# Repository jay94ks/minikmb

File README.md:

# MiniKMB

[한국어](README.md) · [English](README.en.md)

두 대의 미니 PC를 하나의 관리 PC에서 다루기 위해 제작한 USB KVM 프로젝트입니다. HDMI 영상, 키보드·절대좌표 마우스, 시리얼, 가상 디스크와 네트워크 기능을 함께 제공합니다. RP2040 배선 프로토타입에서 시작해 STM32H7 기반 전용 PCB와 Rust 데스크톱 앱으로 발전했습니다.

[Windows 앱·펌웨어 다운로드](https://github.com/jay94ks/minikmb/releases) · [빌드 안내](docs/BUILDING.md) · [하드웨어와 주의사항](docs/HARDWARE.md) · [References](#references)

## 주요 기능

- 보드당 두 채널을 제공하며 여러 보드를 하나의 앱에서 관리합니다. USB 허브의 고정 포트 관계로 MCU와 MS2130을 자동으로 묶고, MCU와 통신해 읽은 UID를 채널 식별자로 사용합니다.
- 채널 이름 변경·저장, 카드 드래그 정렬, 영상 모드 선택과 한 채널의 영상 제어를 지원합니다.
- 실제 키보드, 가상 키보드, 특수 키, 절대좌표 마우스, 클릭·드래그·휠을 전달합니다.
- SD에 ISO/UDF 설치 이미지와 FAT32·exFAT·EXT4 디스크 이미지를 보관합니다. 광학 드라이브와 쓰기 가능한 가상 디스크, 폴더 전달, 이미지 업로드·생성·포맷을 관리합니다.
- CDC 시리얼, NCM 에뮬레이션·호스트 인터넷/LAN 공유, 포트 포워딩과 타깃 포트 스캐너를 제공합니다.
- ST-Link/SWD를 통한 STM32 플래싱과 RP2040 SPI Writer를 통한 MS2130 ROM 기록을 앱에서 실행합니다. 새 보드의 프로그래밍에 채널 선택이나 기존 MCU UID 등록은 필요하지 않습니다.
- 실행 중인 Rust 앱에 Windows Named Pipe로 연결하는 [로컬 CLI](kbm-rs/docs/CLI.md)를 제공합니다. 기본 입력·출력은 개별 옵션과 표·텍스트이며, `--json`으로 JSON을 선택합니다.
- 앱 내 REST 문서와 MCP 연동 안내를 제공합니다. 여러 API 키를 생성·개별 삭제할 수 있으며, 채널 정보·영상 캡처·키보드/마우스·TTY·MSC·NCM을 공통 명령 계층으로 제어합니다.

GUI·REST·MCP·CLI 전체에서 **활성 채널은 한 개**입니다. 채널 선택만 UID를 받고, 일반 제어는 현재 활성 채널에 적용합니다. 마우스 API 좌표는 캡처 영상의 픽셀이며 앱이 HID 절대좌표로 변환합니다. MCP를 켜면 REST도 함께 켜지고 REST 단독 실행도 가능합니다. 대용량 파일은 MCP가 알려주는 REST 업로드 끝점으로 전송합니다.

## 시작하기

1. [Releases](https://github.com/jay94ks/minikmb/releases)에서 Windows x64 ZIP을 받아 새 폴더에 풉니다. `tools/`, `firmware/`, 라이선스 파일을 함께 유지하고 `minikmb-native.exe`를 실행합니다.
2. 보드의 관리 USB **J9**를 관리 PC에 연결합니다. 타깃 0은 **J1 HDMI + J3 USB**, 타깃 1은 **J2 HDMI + J4 USB**를 연결합니다. J7/J8은 각 채널의 microSD입니다.
3. 채널 목록에서 **제어하기**를 누릅니다. 여러 보드를 연결해도 한 번에 한 채널의 영상을 엽니다.
4. 필요에 따라 디스크 공유·시리얼·네트워크 기능을 켭니다. REST/MCP와 네트워크 기능은 기본 OFF입니다.

Windows 10/11 x64, DirectX 12와 Media Foundation을 사용하는 미리보기 앱입니다. Visual C++ v14 x64 Runtime이 필요할 수 있습니다. 새 디스크 이미지의 파일시스템 생성은 WSL의 `mkfs`/`fsck` 도구를 사용합니다. 앱 자체 실행에는 Rust·Node.js·Python 설치가 필요하지 않습니다.

현재 배포 펌웨어는 **STM32 v1.0 / FS-HID r63**이며, Rust 앱 패키지 버전은 **0.1.0 preview**입니다. Electron v1.0 소스도 함께 보존합니다. 타깃 USB는 현재 Full Speed(FS)로 제공합니다. 설계자는 USB-C 삽입 방향 감지·신호 선택 회로의 부재와 그에 따른 HS 경로의 임피던스 불일치를, HS 연결이 안정적으로 수립되지 않거나 연결 후 오류율이 높았던 원인으로 판단하고 있습니다. 이 설계 회고와 검증 범위는 [HS 제한 및 설계 회고](docs/KNOWN-ISSUES.md#타깃-usb-hs와-설계-회고)에 정리했습니다. MS2130의 USB 3.x 영상 경로와 MCU의 USB3300/ULPI 경로는 서로 별개입니다. 자세한 범위는 [알려진 제한](docs/KNOWN-ISSUES.md)을 확인해 주세요.

## 로컬 CLI (최신 소스)

업데이트된 GUI와 `minikmb-cli.exe`를 함께 빌드하면 TCP REST/MCP를 켜거나 API 키를 만들지 않고도 같은 기능을 사용할 수 있습니다. `channels`, `activate UID`, `capture`, 파일 업로드와 이벤트 구독을 제공하며, 61개 공통 API 명령을 `COMMAND --field value` 또는 `call COMMAND`로 호출합니다.

```powershell
.\minikmb-cli.exe channels
.\minikmb-cli.exe schema hid_key_sequence
.\minikmb-cli.exe hid_key_sequence --keys a --keys b --keys c
.\minikmb-cli.exe channels --json
```

키 입력 명령은 활성 타깃을 실제로 제어합니다. [한글 사용법](kbm-rs/docs/CLI.md) · [English](kbm-rs/docs/CLI.en.md). AI 에이전트용 [SKILL.md](kbm-rs/packaging/SKILL.md)도 배포 폴더에 함께 포함합니다. CLI와 에이전트 스킬·REST 문서·독립 HTML 콘솔은 [v1.0.1 릴리스](https://github.com/jay94ks/minikmb/releases/tag/v1.0.1)부터 포함됩니다. [빌드 안내](docs/BUILDING.md)를 참고하세요.

REST 전체 요청의 인자와 예시는 [REST API 문서](kbm-rs/packaging/REST-API.md), 정확한 스키마는 [OpenAPI](kbm-rs/packaging/openapi.json)에 있습니다. [HTML 요청 콘솔](kbm-rs/packaging/REST-API.html)도 함께 배포합니다. HTML 파일을 직접 열고 앱의 REST 주소와 API 키를 입력하면 실제 요청을 실행할 수 있습니다. 별도 웹서버는 필요 없습니다.

## 문서 언어

공개 안내문서는 [한글 문서](docs/README.md)와 [영문 문서](docs/README.en.md)에서 각각 찾을 수 있습니다. 각 안내문서 상단에서 언어를 전환할 수 있습니다. 프로토콜 상세 명세·소스 주석은 개발 참고자료로 연결하고, 제조사 데이터시트와 외부 라이선스 원문은 원래 언어로 보존합니다.

## 개발 과정과 사진

### RP2040 프로토타입

초기 구성은 관리용 RP2040 한 대와 타깃용 RP2040 두 대를 UART로 연결했습니다. HDMI 영상은 별도의 상용 캡처 케이블 두 개를 사용했습니다. 아래 사진은 수작업 배선 프로토타입과 미니 PC 두 대에 설치해 시험했던 구성입니다.

| RP2040 배선 프로토타입 | 상용 캡처 케이블을 사용한 두 대의 미니 PC 시험 |
|---|---|
|  |  |

### STM32H7 기반 전용 보드

새 버전에서는 STM32H743 두 개, USB3300 PHY 두 개, MS2130 캡처 IC 두 개, USB 허브와 microSD 슬롯을 한 PCB에 통합했습니다. MCU 펌웨어는 TinyUSB·FreeRTOS·FatFs를 이용합니다.

| 디버깅·펌웨어 개발 단계 | 미니 PC 두 대에 연결한 전용 보드 |
|---|---|
|  |  |

### H7 보드를 위한 MS2130 ROM 플래싱 도구와 SMT 검사

왼쪽 도구는 **STM32H7 보드에 탑재한 MS2130을 실제로 동작시키기 위해 제작한 RP2040 기반 SPI ROM Writer**입니다. 초기 KVM 프로토타입과는 역할이 다릅니다. 외부 SPI 플래시에 MS2130 펌웨어를 기록한 뒤 영상 입력이 동작했습니다. 오른쪽은 SMT 조립 공정 이후 촬영한 X-ray입니다. 사진 자체를 보드 전체의 전기적·신호 무결성 검증 결과로 해석하지는 않습니다.

| MS2130용 SPI ROM Writer | SMT 조립 후 X-ray |
|---|---|
|  |  |

### PC 앱

Electron 앱을 바탕으로 Rust·egui 앱을 구현했습니다. 채널을 묶어 관리하고, 선택한 타깃의 영상과 입력·저장소·네트워크를 제어합니다. 아래는 채널 목록과 MCP 연동 안내 화면입니다. 스크린샷은 개발 당시의 장치 상태를 보여 줍니다.

## 저장소 구성

| 위치 | 내용 |
|---|---|
| [`hardware/stm32h7/`](hardware/stm32h7/) | 실제 제작한 6층 PCB·회로도·프로젝트 로컬 라이브러리·Gerber·조립 BOM/CPL |
| [`hardware/case/`](hardware/case/) | 나사 없는 투명 케이스 시안, FreeCAD 원본과 JLC3DP용 STL·STEP |
| [`hardware/rp2040/`](hardware/rp2040/) | 수작업 RP2040 프로토타입 배선 안내 |
| [`hardware/prototypes/`](hardware/prototypes/) | 초기 부품 라이브러리와 미완성 MS2130 단독 시험 보드. 제조용 아님 |
| [`firmware/stm32h7/`](firmware/stm32h7/) | 현재 STM32H743 펌웨어, STM32CubeIDE 프로젝트, 프로토콜·메모리맵·테스트 |
| [`master/`](master/), [`slave/kbm-slave/`](slave/kbm-slave/), [`common/`](common/) | RP2040 관리 브리지·타깃 펌웨어와 공통 프로토콜/호스트 테스트 |
| [`firmware/flash-writer/`](firmware/flash-writer/) | RP2040 SPI Writer 펌웨어와 호스트 도구 소스 |
| [`kbm/`](kbm/) | Electron·Quasar·Vue·TypeScript 앱 |
| [`kbm-rs/`](kbm-rs/) | 현재 Rust·egui·wgpu 앱, 로컬 CLI와 REST/MCP 서버 |
| [`work/`](work/) | 하드웨어 입력을 발생시키지 않는 회귀 테스트와 앱 빌드 보조 도구 |
| [`vendor/`](vendor/) | 고정 라이브러리 원본 아카이브, SDK, GPL 대응 소스와 체크섬 |
| [`references/`](references/) | 사용 칩셋 목록·데이터시트·출처·자료별 권리 고지 |
| [`docs/`](docs/) | 빌드·사용 범위·하드웨어 설명과 개발 사진 |

원래 RP2040 소스의 상대 경로를 유지하기 위해 `master`/`slave`/`common`과 두 앱의 디렉터리 이름을 유지했습니다. 빌드 캐시, 개인 설정·API 키, 장치 캡처 로그, 프롬프트·대화 기록은 공개 소스에 포함하지 않습니다.

## 개발 및 검증

[빌드 안내](docs/BUILDING.md)에 Windows 앱, WSL RP2040, STM32CubeIDE와 포터블 ARM 빌드 절차를 정리했습니다. 하드웨어와 독립적인 테스트는 [테스트 안내](docs/TESTING.md)를 참조해 주세요. 단위 테스트 통과, 펌웨어 빌드, 실제 타깃 동작 확인은 구분합니다.

**회로도는 제작자 jay94ks가 직접 작성했습니다.** 타깃 USB-C의 방향 감지·신호 선택 구성과 HS 경로의 임피던스 조건을 충분히 검토하지 않은 채 PCB 아트웍으로 진행한 것이 이번 설계의 검토 누락이었습니다. 이 문제를 GPT가 회로도를 잘못 작성한 결과로 기록하지 않습니다.

이 프로젝트는 **OpenAI Codex의 GPT 6 Astra와 Sol을 활용하여 개발**했습니다. 제작자가 회로도 작성·하드웨어 제작·연결·납땜·실사용 확인을 수행했으며, 두 모델은 PCB 배치·배선 작업, 펌웨어·앱 구현과 문서화에 활용했습니다.

## 라이선스

직접 작성한 코드와 설계·문서는 [MIT License](LICENSE)로 공개합니다. **아래 외부 구성 요소까지 MIT로 재허가하는 것은 아닙니다.** 원래 저작권·라이선스·예외 조항이 우선하며, 자료별 적용 범위는 [라이선스 고지](NOTICE.ko.md)와 [References](references/README.md)에 정리했습니다.

| 구성 요소 | 적용 조건과 고지 |
|---|---|
| MiniKMB 직접 작성 코드·설계·문서 | MIT. 기존 외부 코드/데이터와 개별 SPDX 고지는 제외 |
| TinyUSB, FreeRTOS | MIT. 원본 LICENSE 보존 |
| Pico SDK, STM32 HAL, CMSIS | SDK/파일별 BSD-3-Clause·Apache-2.0 등 원문 조건 보존 |
| FatFs | ChaN의 원래 저작권 및 허용 고지 보존 |
| Rust·Electron 의존성 | lock 파일로 고정. [원본 아카이브](vendor/README.md)와 각 패키지의 LICENSE/NOTICE, [Windows 앱 의존성 고지](kbm-rs/licenses/THIRD-PARTY.md) 참조 |
| probe-rs | MIT OR Apache-2.0. 앱에서 별도 실행 파일로 호출 |
| flashrom·MS2130 SPI helper | GPL-2.0 계열/파일별 고지. [대응 소스](vendor/flashrom/)와 원래 COPYING 포함. 별도 프로세스로 실행 |
| Noto Sans KR / Lucide | SIL OFL-1.1 / ISC 및 MIT(Feather 유래 부분). [글꼴·아이콘 고지](kbm-rs/assets/fonts/) 참조 |
| KiCad 표준 라이브러리·공급사 유래 형상 | 원래 라이선스와 KiCad 예외/공급사 출처 고지 보존. [CAD 출처](hardware/stm32h7/libraries/README.md) 참조 |
| 데이터시트·칩셋 문서·MS2130 ROM | 제조사/원 저작권자의 권리 유지. MIT 대상 아님. MS2130 ROM의 별도 공개 라이선스는 확인되지 않음 |

프로젝트 사진은 제작자가 공개용으로 제공한 개발 기록입니다. 제품명·상표·화면에 보이는 외부 소프트웨어의 권리는 해당 권리자에게 있습니다.

## References

칩셋 목록과 회로도 참조번호는 [chipsets.csv](references/chipsets.csv), 수집한 원문과 SHA-256은 [데이터시트 목록](references/README.md), 라이브러리 버전·원본은 [vendor/README.md](vendor/README.md)에 있습니다. 다운로드할 수 없었던 자료도 원본 링크와 상태를 남겼습니다.

- **STM32H743** — [ST 데이터시트](https://www.st.com/resource/en/datasheet/stm32h743vi.pdf), [RM0433](https://www.st.com/resource/en/reference_manual/rm0433-stm32h742-stm32h743753-and-stm32h750-value-line-advanced-armbased-32bit-mcus-stmicroelectronics.pdf)
- **USB3300** — [Microchip DS00001783](https://ww1.microchip.com/downloads/aemDocuments/documents/UNG/ProductDocuments/DataSheets/USB3300-Data-Sheet-DS00001783.pdf)
- **MS2130 / GL3510-OSY52 / CH482X** — [수집한 데이터시트와 공급처 출처](references/README.md). 초기 검토용 GL3523 자료는 실제 GL3510 부품과 구분합니다.
- **LM26480 / TUSB321 / XC6220 / USBLC6-2 / W25Q16JV** — [칩셋·전원·보호·SPI 메모리 자료](references/README.md)
- **RP2040 / Pico SDK** — [RP2040 데이터시트](https://datasheets.raspberrypi.com/rp2040/rp2040-datasheet.pdf), [Pico SDK](https://github.com/raspberrypi/pico-sdk)
- **TinyUSB / FreeRTOS / FatFs / CMSIS / STM32 HAL** — [hathach/tinyusb](https://github.com/hathach/tinyusb), [FreeRTOS-Kernel](https://github.com/FreeRTOS/FreeRTOS-Kernel), [FatFs](https://elm-chan.org/fsw/ff/), [CMSIS](https://github.com/ARM-software/CMSIS_5), [STM32H7 HAL](https://github.com/STMicroelectronics/stm32h7xx-hal-driver)
- **PC 앱** — [egui/eframe](https://github.com/emilk/egui), [wgpu](https://github.com/gfx-rs/wgpu), [Tokio](https://tokio.rs/), [Axum](https://github.com/tokio-rs/axum), [Rust MCP SDK](https://github.com/modelcontextprotocol/rust-sdk), [smoltcp](https://github.com/smoltcp-rs/smoltcp), [Electron](https://www.electronjs.org/), [Quasar](https://quasar.dev/), [Vue](https://vuejs.org/)
- **플래싱 도구** — [probe-rs](https://github.com/probe-rs/probe-rs), [flashrom](https://github.com/flashrom/flashrom)
- **PCB 제작 검토** — [JLCPCB capabilities](https://jlcpcb.com/capabilities/pcb-capabilities), [임피던스 계산기](https://jlcpcb.com/pcb-impedance-calculator). 저장된 스택업·제조 조건은 [하드웨어 안내](docs/HARDWARE.md) 참조

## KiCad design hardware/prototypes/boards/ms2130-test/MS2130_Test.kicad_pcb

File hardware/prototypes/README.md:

# Early hardware studies

This directory preserves early candidate symbols, footprints, pin maps and the incomplete MS2130 test board. These are historical studies, not the fabricated STM32H7 board. The MS2130 test PCB is not fully routed and must not be submitted for fabrication as a finished design. Experimental auto-router outputs and private validation journals are excluded.

The actual board uses GL3510-OSY52, not the GL3523 candidate documented here. Manufacturer references and JLCEDA/EasyEDA attribution are in `references/SOURCES.md`. Original KiCad-derived geometry retains its upstream library license and exception.

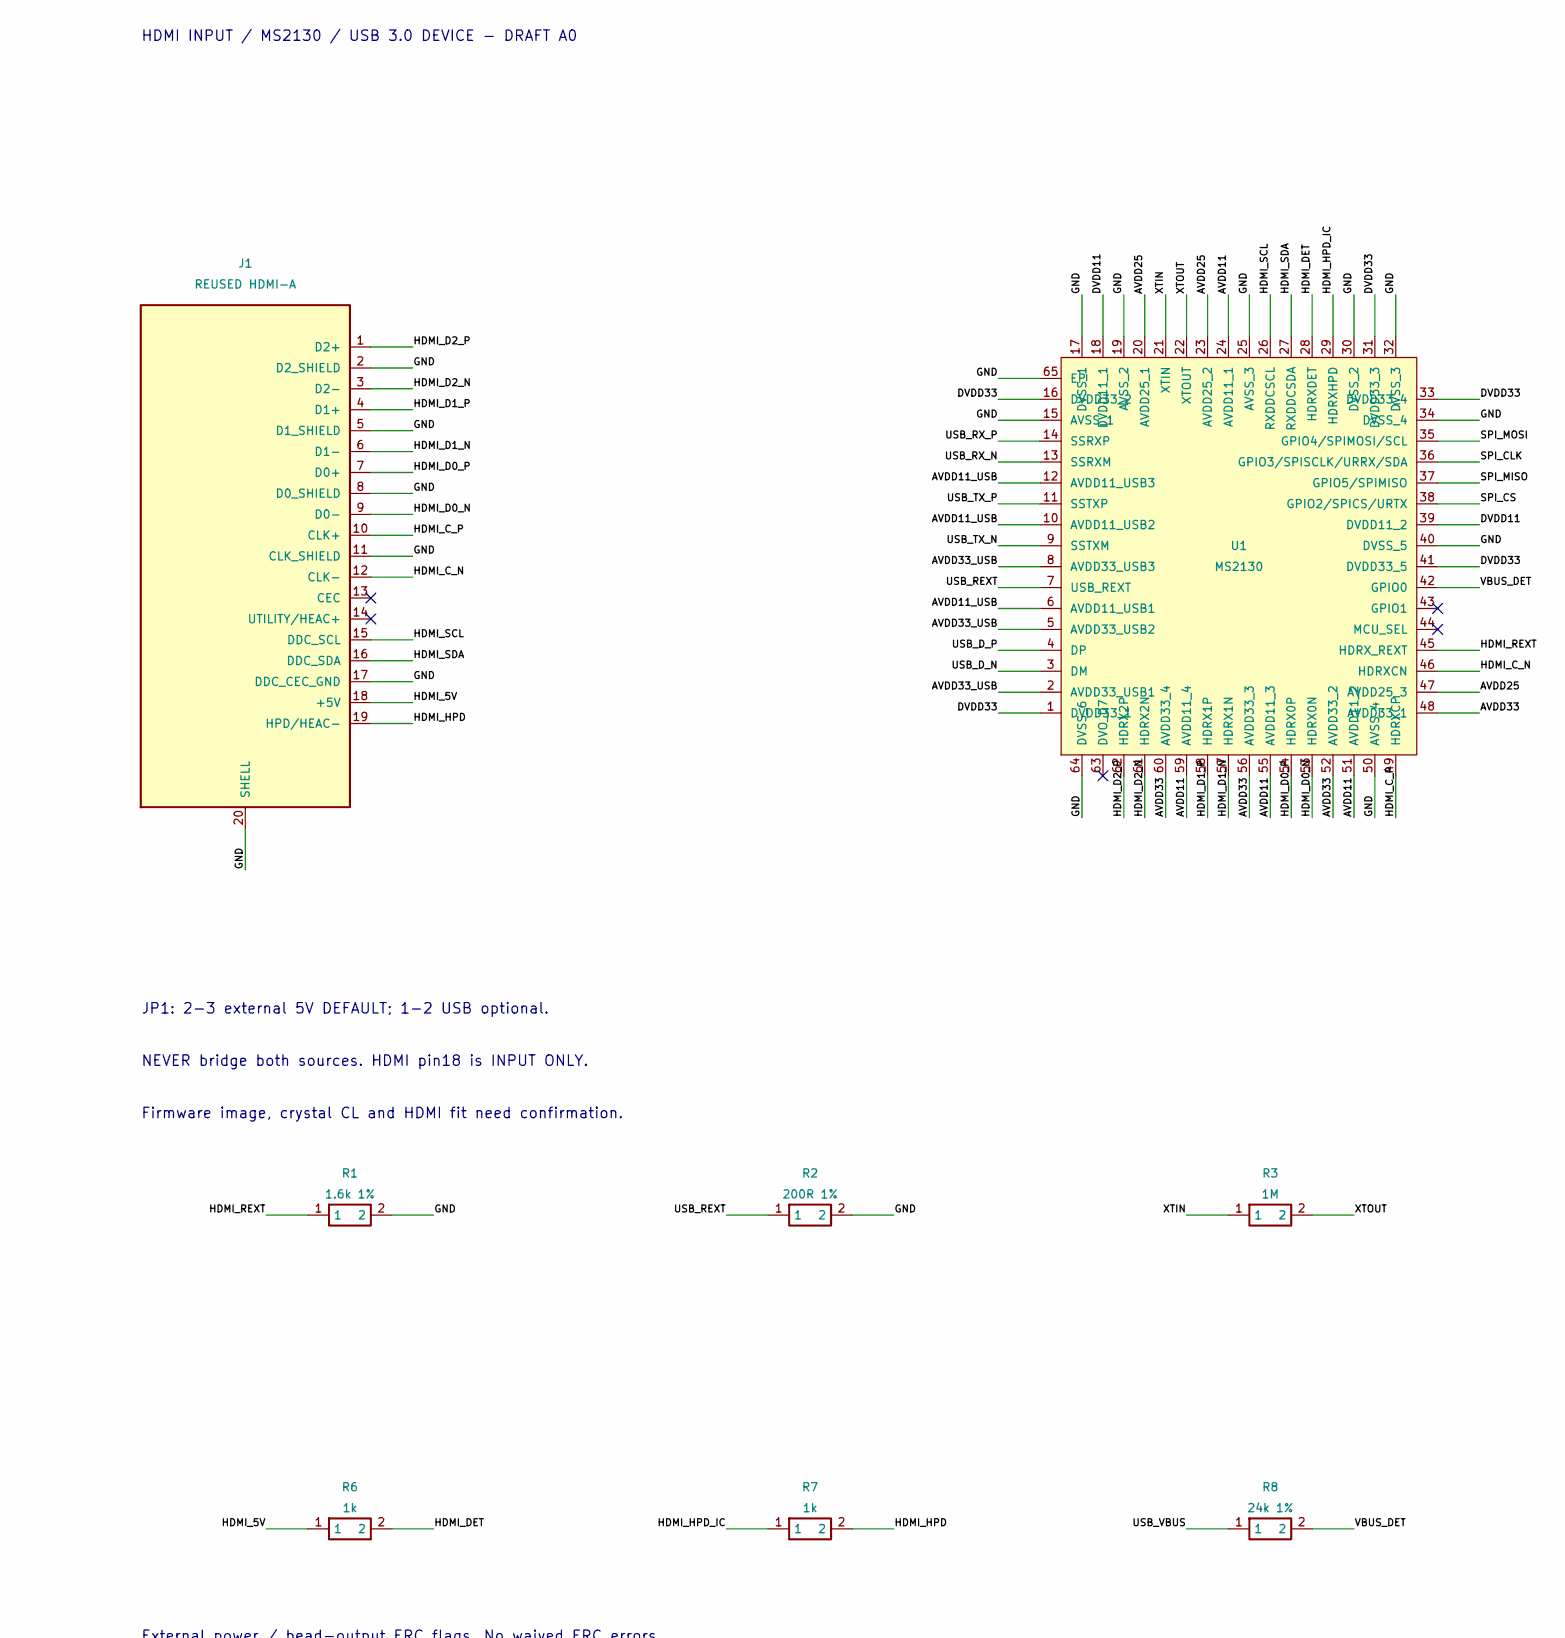
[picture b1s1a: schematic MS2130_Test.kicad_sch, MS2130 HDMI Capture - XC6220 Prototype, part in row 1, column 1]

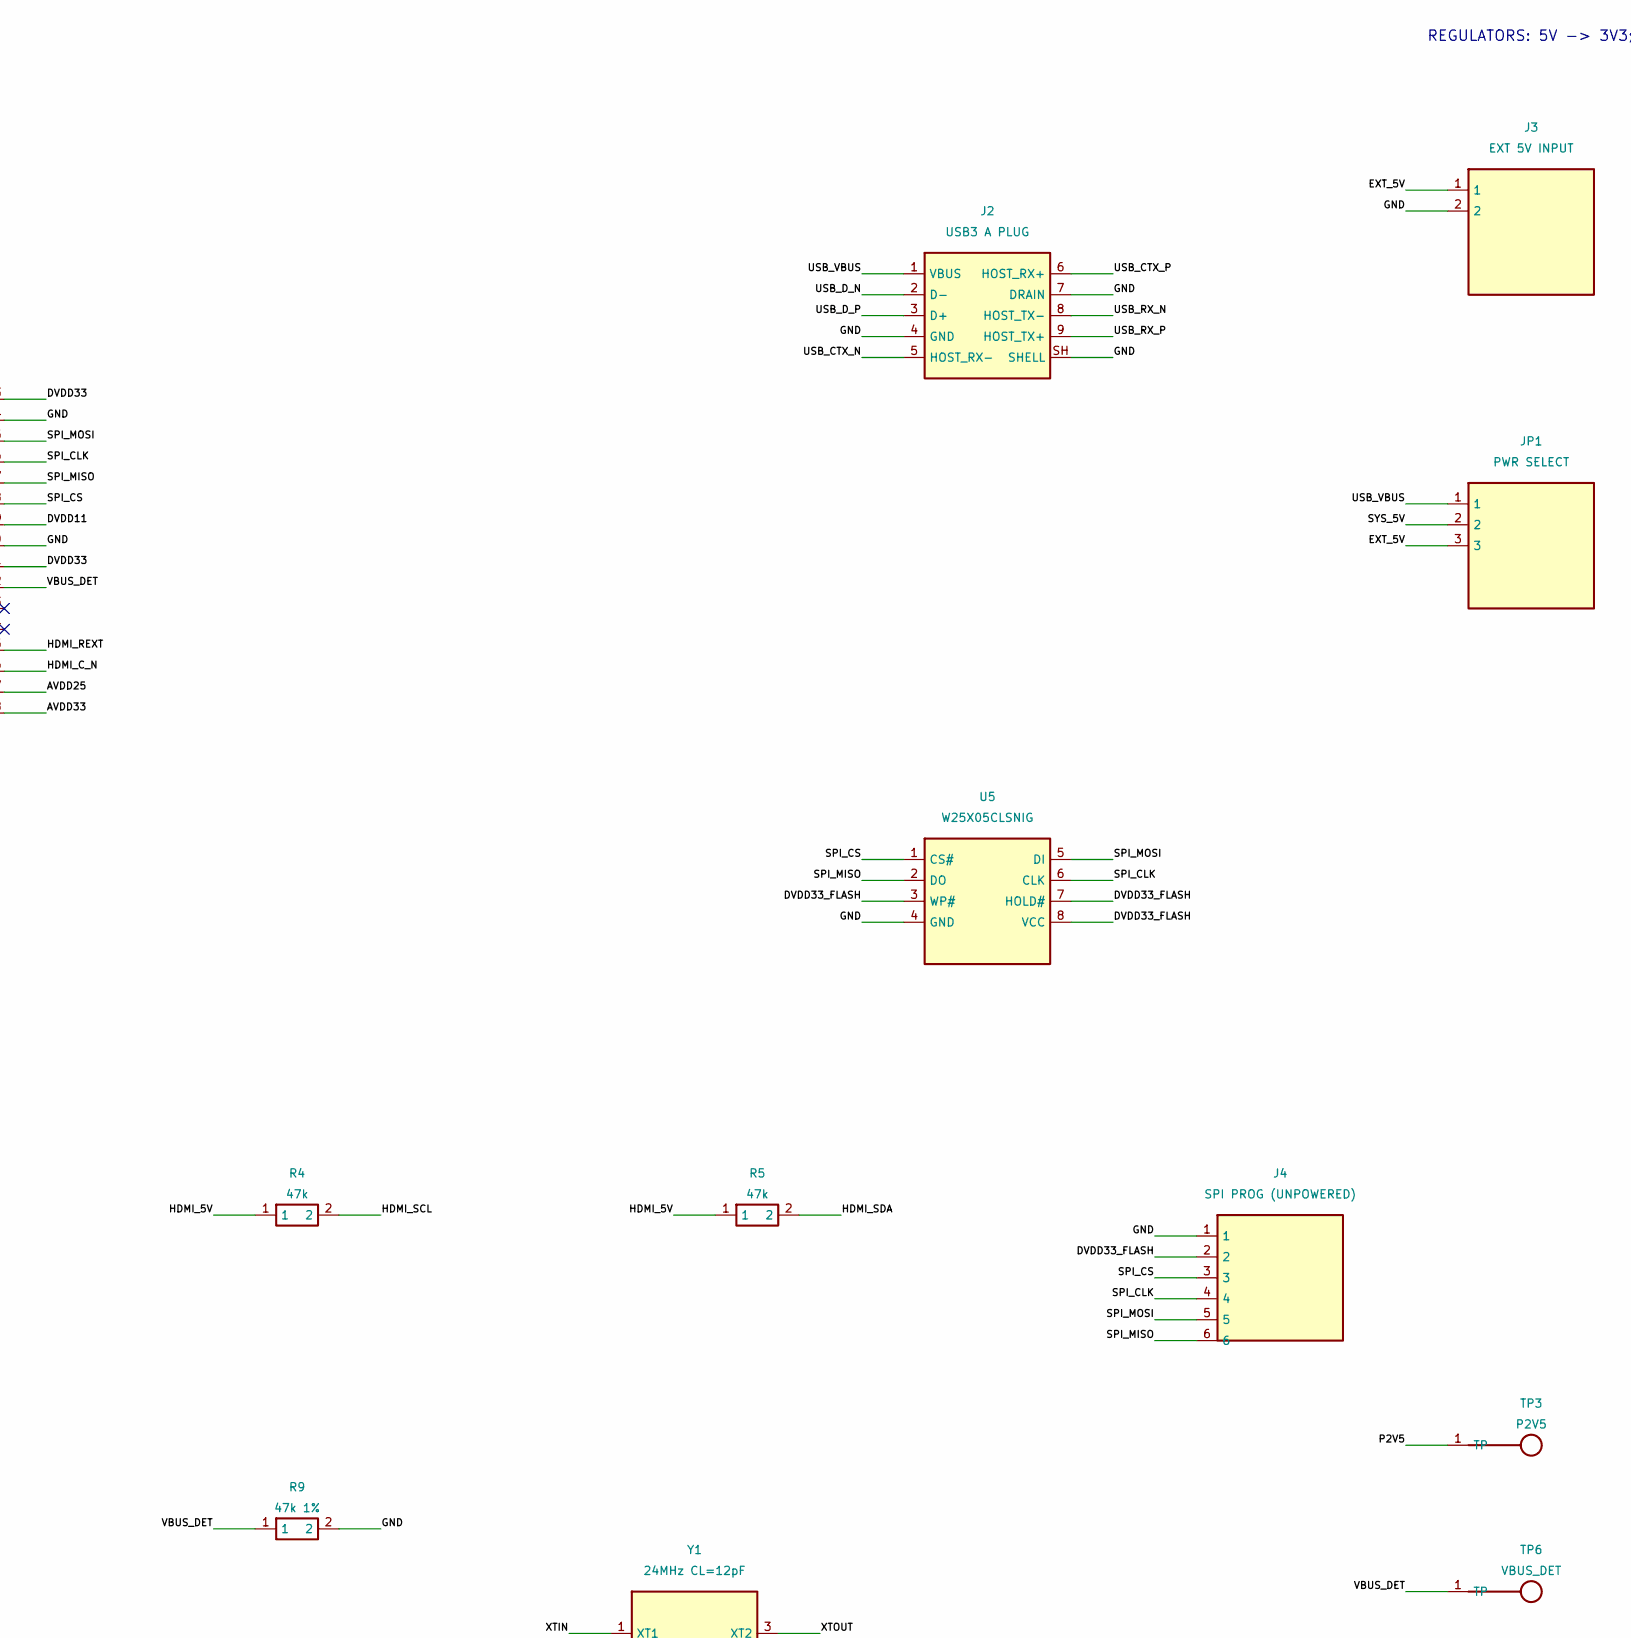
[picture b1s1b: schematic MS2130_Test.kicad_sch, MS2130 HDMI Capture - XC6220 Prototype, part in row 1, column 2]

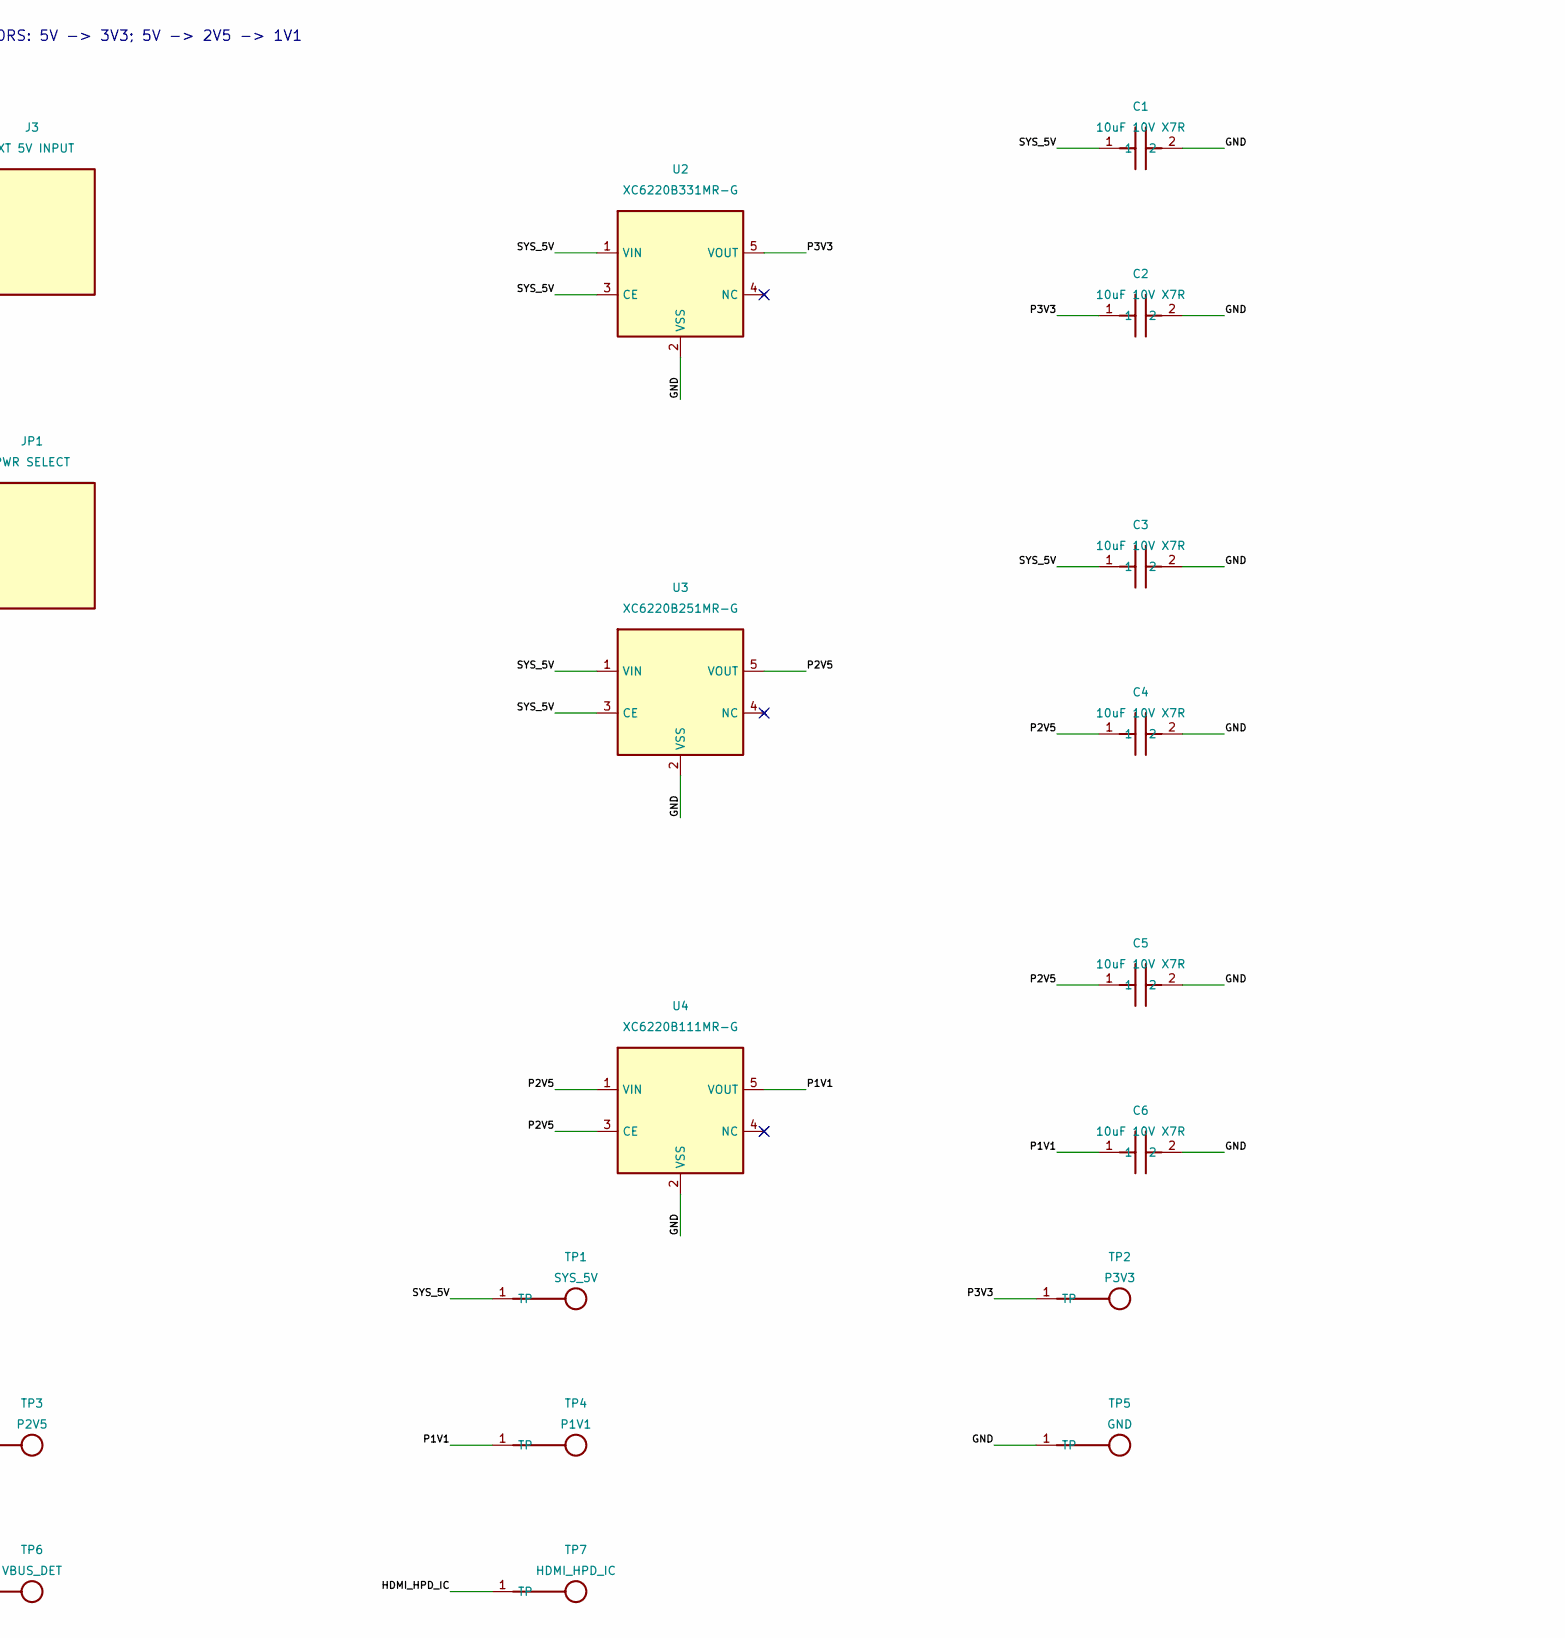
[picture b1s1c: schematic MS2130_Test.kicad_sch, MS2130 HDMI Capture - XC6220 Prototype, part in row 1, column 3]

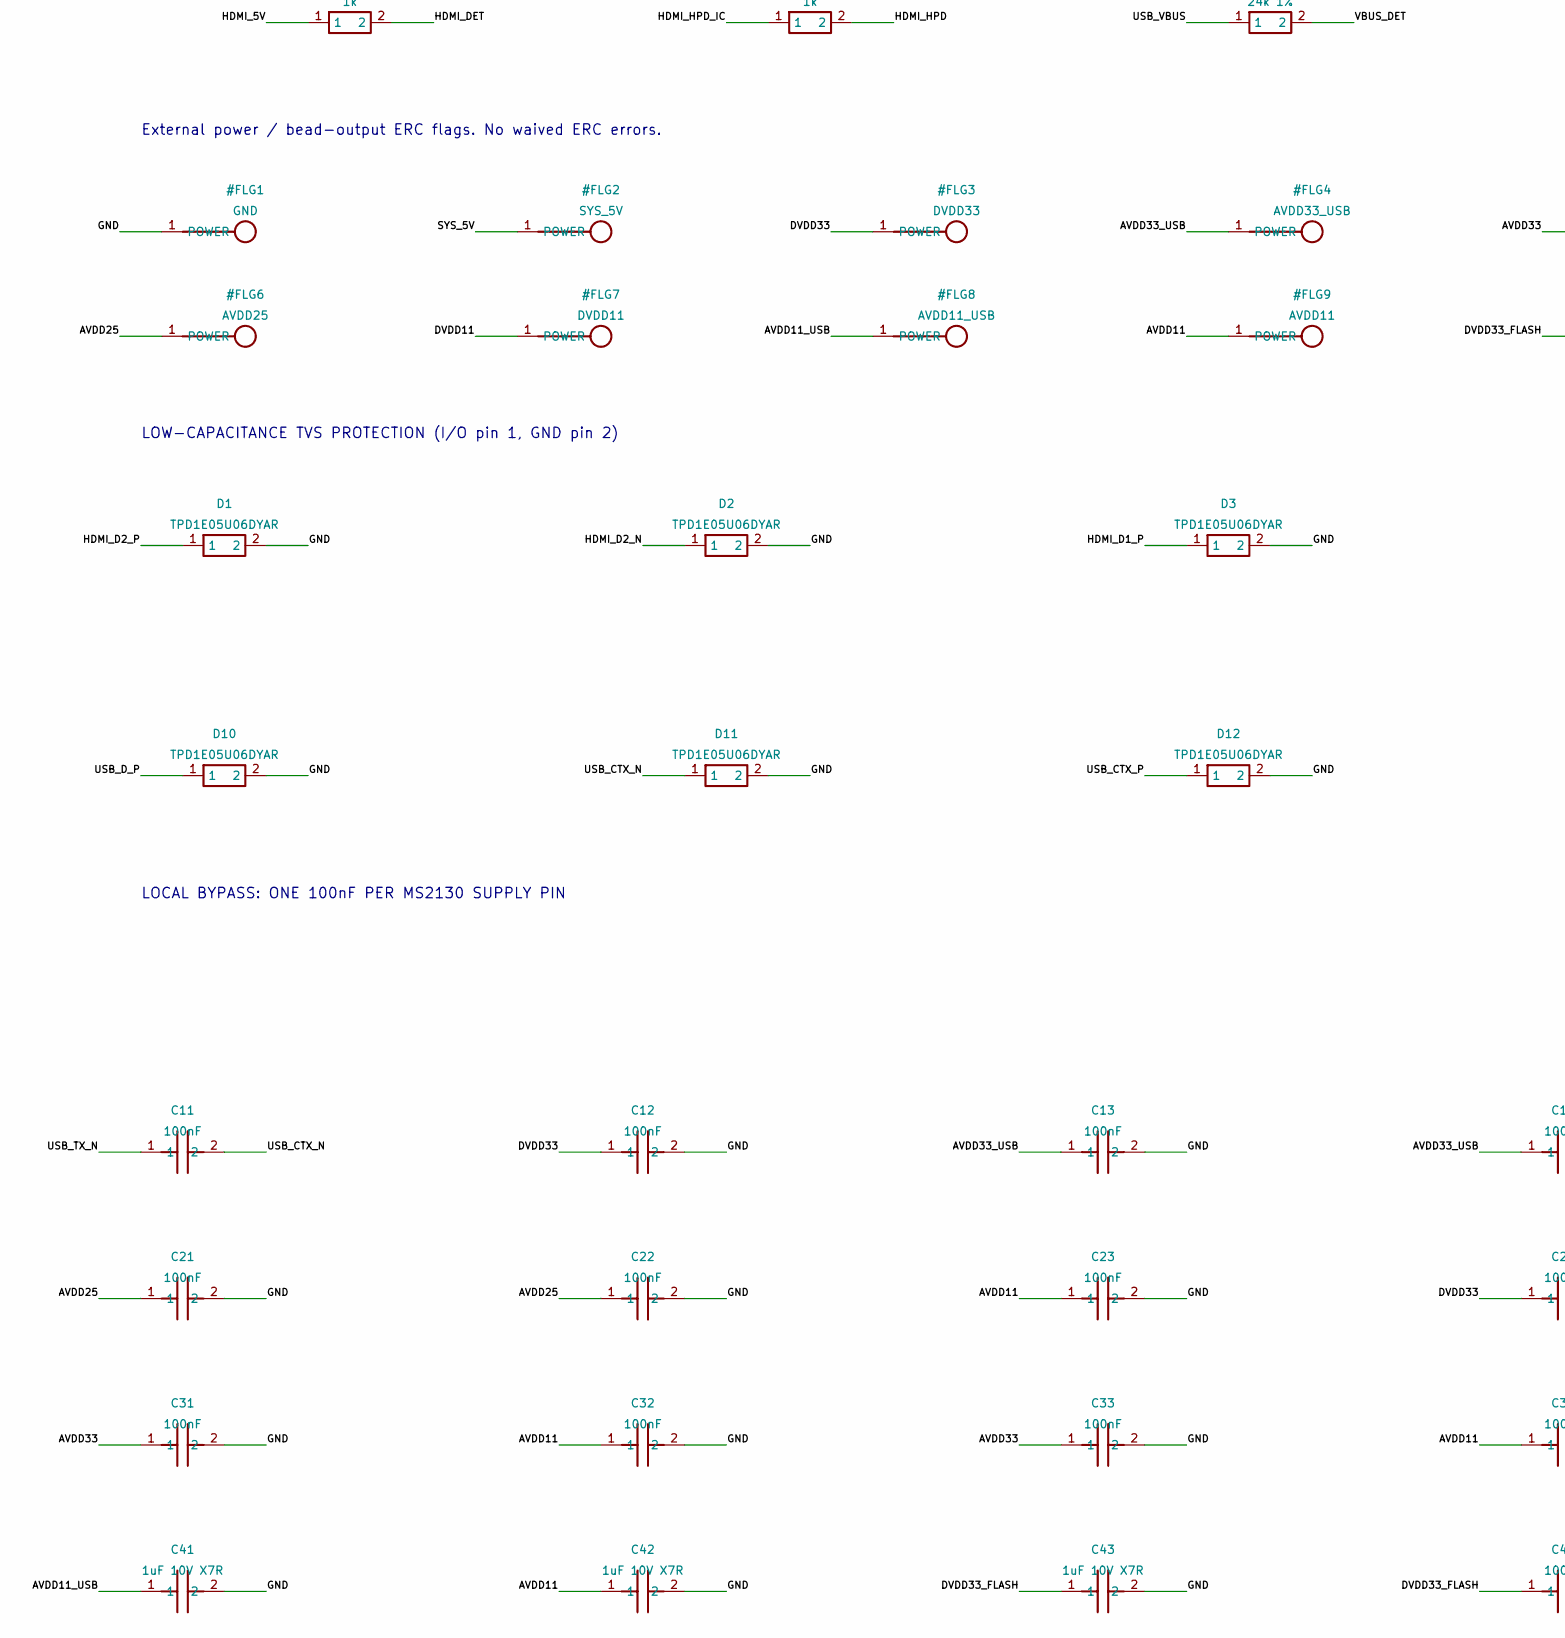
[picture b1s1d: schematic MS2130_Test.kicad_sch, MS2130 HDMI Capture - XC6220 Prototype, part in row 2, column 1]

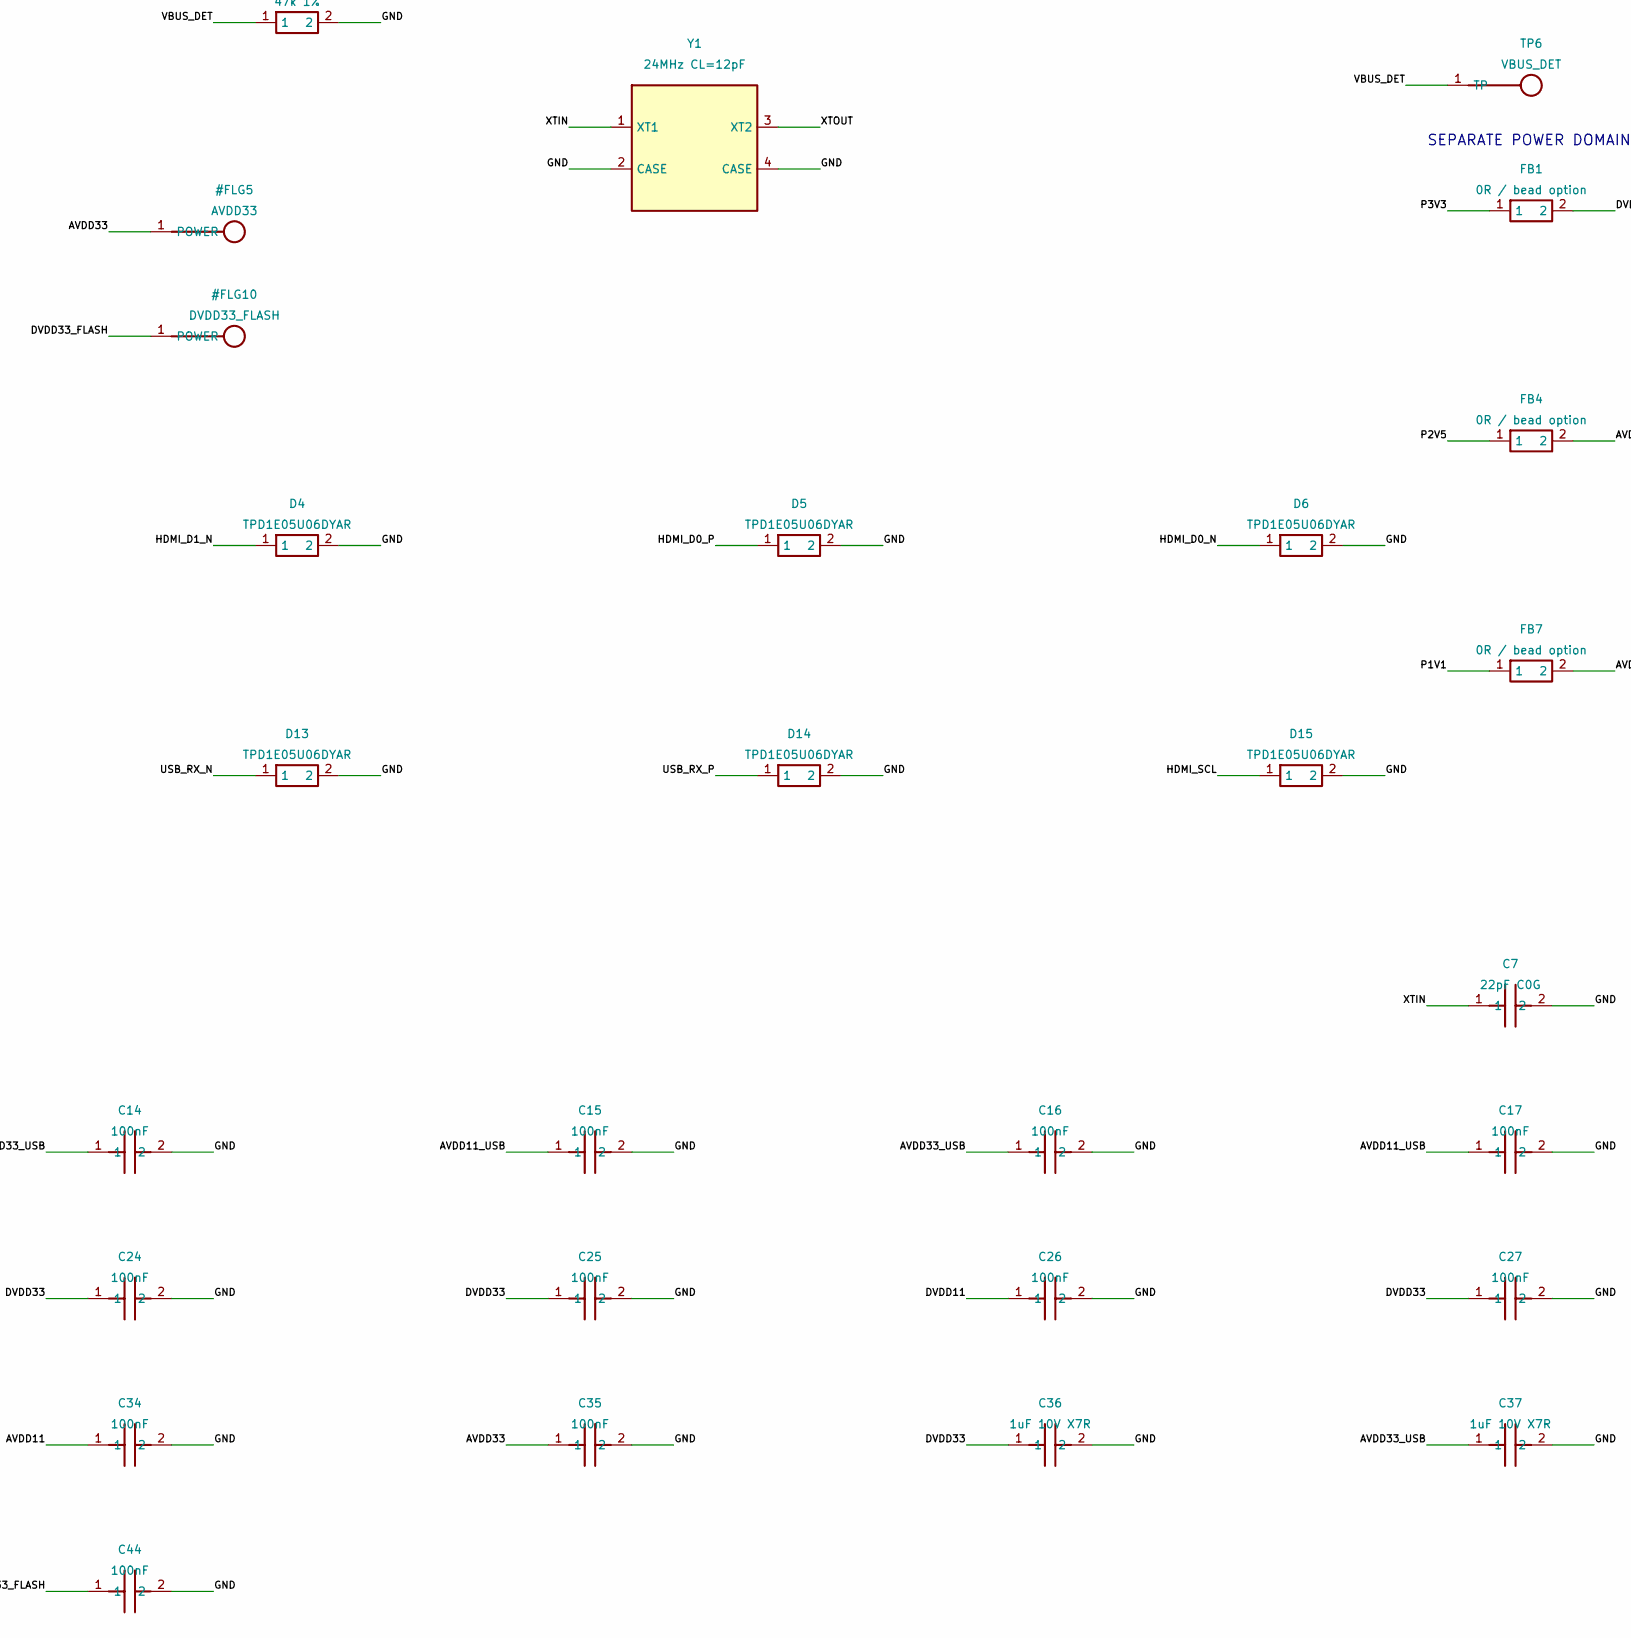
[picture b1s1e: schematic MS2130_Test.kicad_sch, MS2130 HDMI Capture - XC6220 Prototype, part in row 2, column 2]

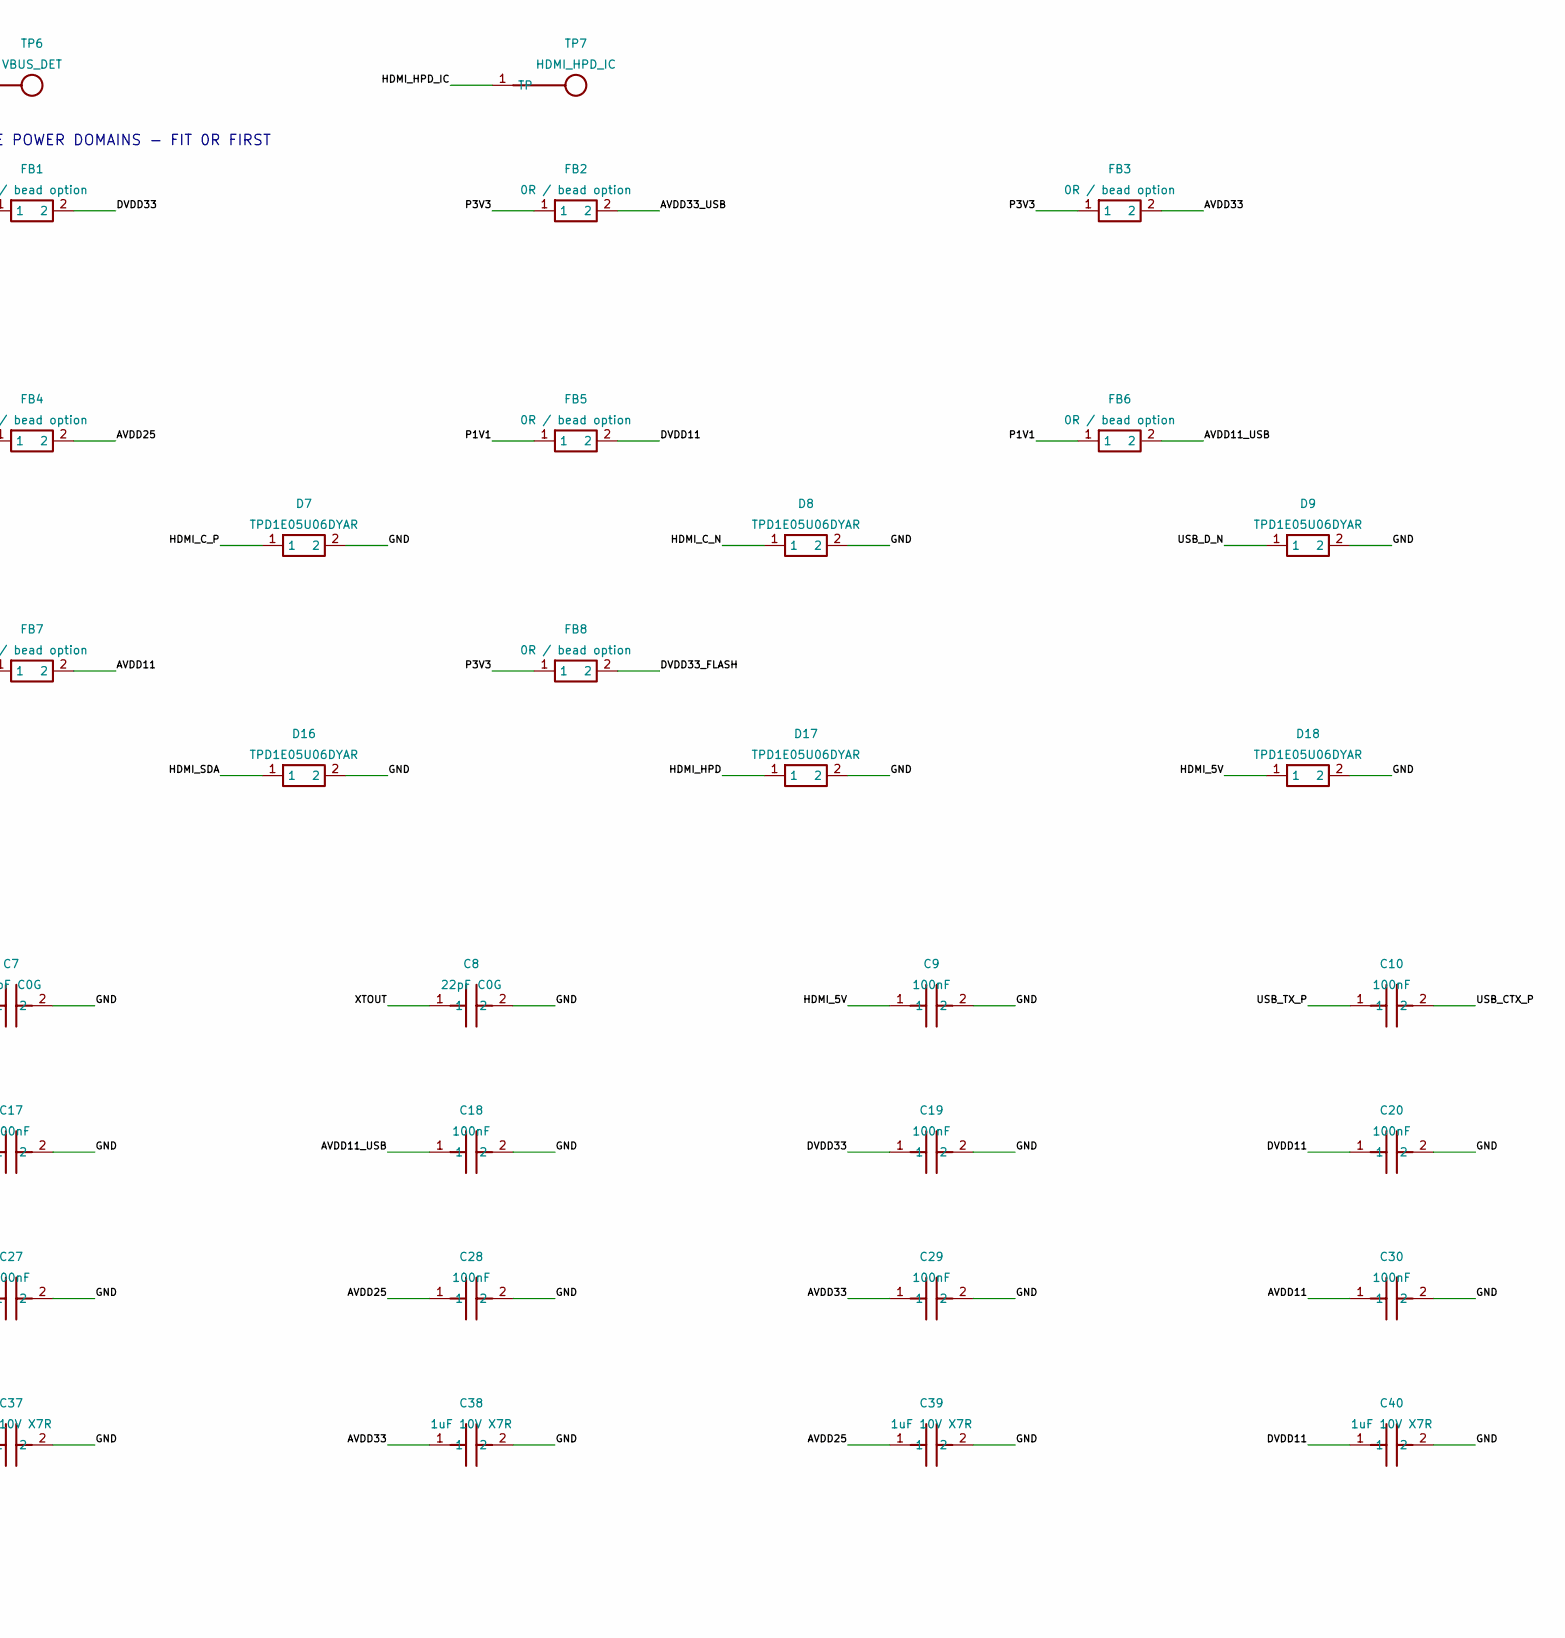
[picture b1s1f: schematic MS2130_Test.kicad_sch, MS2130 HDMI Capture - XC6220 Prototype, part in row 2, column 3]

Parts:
C1, C2, C3, C4, C5, C6: 10uF 10V X7R; C_0603_1608Metric
C7, C8: 22pF C0G; C_0603_1608Metric
C9, C10, C11, C12, C13, C14, C15, C16, C17, C18, C19, C20, C21, C22, C23, C24, C25, C26, C27, C28, C29, C30, C31, C32, C33, C34, C35, C44: 100nF; C_0603_1608Metric
C36, C37, C38, C39, C40, C41, C42, C43: 1uF 10V X7R; C_0603_1608Metric
D1, D2, D3, D4, D5, D6, D7, D8, D9, D10, D11, D12, D13, D14, D15, D16, D17, D18: TPD1E05U06DYAR; D_SOD-523
FB1, FB2, FB3, FB4, FB5, FB6, FB7, FB8: 0R / bead option; R_0603_1608Metric
J1: REUSED HDMI-A; HDMI_A_19P_Reused_WFD6_Compatible
J2: USB3 A PLUG; USB3_A_Plug_Wuerth_692112030100_Horizontal
J3: EXT 5V INPUT; PinHeader_1x02_P2.54mm_Vertical
J4: SPI PROG (UNPOWERED); PinHeader_1x06_P2.54mm_Vertical
JP1: PWR SELECT; PinHeader_1x03_P2.54mm_Vertical
R1: 1.6k 1%; R_0603_1608Metric
R2: 200R 1%; R_0603_1608Metric
R3: 1M; R_0603_1608Metric
R4, R5: 47k; R_0603_1608Metric
R6, R7: 1k; R_0603_1608Metric
R8: 24k 1%; R_0603_1608Metric
R9: 47k 1%; R_0603_1608Metric
TP1: SYS_5V; TestPoint_Pad_D1.5mm
TP2: P3V3; TestPoint_Pad_D1.5mm
TP3: P2V5; TestPoint_Pad_D1.5mm
TP4: P1V1; TestPoint_Pad_D1.5mm
TP5: GND; TestPoint_Pad_D1.5mm
TP6: VBUS_DET; TestPoint_Pad_D1.5mm
TP7: HDMI_HPD_IC; TestPoint_Pad_D1.5mm
U1: MS2130; QFN-64-1EP_9x9mm_P0.5mm_EP5.7x5.7mm_MS2130
U2: XC6220B331MR-G; SOT-23-5
U3: XC6220B251MR-G; SOT-23-5
U4: XC6220B111MR-G; SOT-23-5
U5: W25X05CLSNIG; SOIC-8_3.9x4.9mm_P1.27mm
Y1: 24MHz CL=12pF; Crystal_SMD_3225-4Pin_3.2x2.5mm

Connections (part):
/AVDD11: C23.1, C30.1, C32.1, C34.1, C42.1, FB7.2, U1.24 (AVDD11_1), U1.51 (AVDD11_2), U1.55 (AVDD11_3), U1.59 (AVDD11_4)
/AVDD11_USB: C15.1, C17.1, C18.1, C41.1, FB6.2, U1.6 (AVDD11_USB1), U1.10 (AVDD11_USB2), U1.12 (AVDD11_USB3)
/AVDD25: C21.1, C22.1, C28.1, C39.1, FB4.2, U1.20 (AVDD25_1), U1.23 (AVDD25_2), U1.47 (AVDD25_3)
/AVDD33: C29.1, C31.1, C33.1, C35.1, C38.1, FB3.2, U1.48 (AVDD33_1), U1.52 (AVDD33_2), U1.56 (AVDD33_3), U1.60 (AVDD33_4)
/AVDD33_USB: C13.1, C14.1, C16.1, C37.1, FB2.2, U1.2 (AVDD33_USB1), U1.5 (AVDD33_USB2), U1.8 (AVDD33_USB3)
/DVDD11: C20.1, C26.1, C40.1, FB5.2, U1.18 (DVDD11_1), U1.39 (DVDD11_2)
/DVDD33: C12.1, C19.1, C24.1, C25.1, C27.1, C36.1, FB1.2, U1.1 (DVDD33_1), U1.16 (DVDD33_2), U1.31 (DVDD33_3), U1.33 (DVDD33_4), U1.41 (DVDD33_5)
/DVDD33_FLASH: C43.1, C44.1, FB8.2, J4.2, U5.3 (WP#), U5.7 (HOLD#), U5.8 (VCC)
/EXT_5V: J3.1, JP1.3
/GND: C1.2, C2.2, C3.2, C4.2, C5.2, C6.2, C7.2, C8.2, C9.2, C12.2, C13.2, C14.2, C15.2, C16.2, C17.2, C18.2, C19.2, C20.2, C21.2, C22.2, C23.2, C24.2, C25.2, C26.2, C27.2, C28.2, C29.2, C30.2, C31.2, C32.2, C33.2, C34.2, C35.2, C36.2, C37.2, C38.2, C39.2, C40.2, C41.2, C42.2, C43.2, C44.2, D1.2, D2.2, D3.2, D4.2, D5.2, D6.2, D7.2, D8.2, D9.2, D10.2, D11.2, D12.2, D13.2, D14.2, D15.2, D16.2, D17.2, D18.2, J1.2 (D2_SHIELD), J1.5 (D1_SHIELD), J1.8 (D0_SHIELD), J1.11 (CLK_SHIELD), J1.17 (DDC_CEC_GND), J1.20 (SHELL), J2.4 (GND), J2.7 (DRAIN), J2.SH (SHELL), J3.2, J4.1, R1.2, R2.2, R9.2, TP5.1, U1.15 (AVSS_1), U1.17 (DVSS_1), U1.19 (AVSS_2), U1.25 (AVSS_3), U1.30 (DVSS_2)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
/HDMI_5V: C9.1, D18.1, J1.18 (+5V), R4.1, R5.1, R6.1
/HDMI_C_N: D8.1, J1.12 (CLK-), U1.46 (HDRXCN)
/HDMI_C_P: D7.1, J1.10 (CLK+), U1.49 (HDRXCP)
/HDMI_D0_N: D6.1, J1.9 (D0-), U1.53 (HDRX0N)
/HDMI_D0_P: D5.1, J1.7 (D0+), U1.54 (HDRX0P)
/HDMI_D1_N: D4.1, J1.6 (D1-), U1.57 (HDRX1N)
/HDMI_D1_P: D3.1, J1.4 (D1+), U1.58 (HDRX1P)
/HDMI_D2_N: D2.1, J1.3 (D2-), U1.61 (HDRX2N)
/HDMI_D2_P: D1.1, J1.1 (D2+), U1.62 (HDRX2P)
/HDMI_DET: R6.2, U1.28 (HDRXDET)
/HDMI_HPD: D17.1, J1.19 (HPD/HEAC-), R7.2
/HDMI_HPD_IC: R7.1, TP7.1, U1.29 (HDRXHPD)
/HDMI_REXT: R1.1, U1.45 (HDRX_REXT)
/HDMI_SCL: D15.1, J1.15 (DDC_SCL), R4.2, U1.26 (RXDDCSCL)
/HDMI_SDA: D16.1, J1.16 (DDC_SDA), R5.2, U1.27 (RXDDCSDA)
/P1V1: C6.1, FB5.1, FB6.1, FB7.1, TP4.1, U4.5 (VOUT)
/P2V5: C4.1, C5.1, FB4.1, TP3.1, U3.5 (VOUT), U4.1 (VIN), U4.3 (CE)
/P3V3: C2.1, FB1.1, FB2.1, FB3.1, FB8.1, TP2.1, U2.5 (VOUT)
/SPI_CLK: J4.4, U1.36 (GPIO3/SPISCLK/URRX/SDA), U5.6 (CLK)
/SPI_CS: J4.3, U1.38 (GPIO2/SPICS/URTX), U5.1 (CS#)
/SPI_MISO: J4.6, U1.37 (GPIO5/SPIMISO), U5.2 (DO)
/SPI_MOSI: J4.5, U1.35 (GPIO4/SPIMOSI/SCL), U5.5 (DI)
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
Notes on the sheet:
HDMI INPUT / MS2130 / USB 3.0 DEVICE - DRAFT A0
REGULATORS: 5V -> 3V3; 5V -> 2V5 -> 1V1
LOW-CAPACITANCE TVS PROTECTION (I/O pin 1, GND pin 2)
LOCAL BYPASS: ONE 100nF PER MS2130 SUPPLY PIN
SEPARATE POWER DOMAINS - FIT 0R FIRST
External power / bead-output ERC flags. No waived ERC errors.
JP1: 2-3 external 5V DEFAULT; 1-2 USB optional.
NEVER bridge both sources. HDMI pin18 is INPUT ONLY.
Firmware image, crystal CL and HDMI fit need confirmation.
